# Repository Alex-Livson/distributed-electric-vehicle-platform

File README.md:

# Distributed Electric Vehicle Control and Autonomy Platform

A small-scale electric vehicle electronics platform built around **three custom ESP32-based ECUs and a Raspberry Pi 4 supervisory controller**, connected through a **500 kbps CAN network**.

The project was built as a hands-on study of automotive embedded systems, custom PCB design, distributed vehicle electronics, safety-oriented control, Raspberry Pi development, and computer vision.

## Demo

[Watch the Vehicle Demo](https://youtu.be/MoWJwQRdX8E)

The demonstration includes manual driving, RFID authorization, assisted collision protection, live vehicle telemetry, and OpenCV-assisted autonomous obstacle avoidance.

---

## Project Overview

The vehicle uses a distributed control architecture similar in concept to a simplified electric vehicle.

Instead of one microcontroller handling the entire system, responsibilities are divided between several networked controllers:

* **Battery ECU** – monitors pack voltage, current, temperature, and battery health
* **Sensor ECU** – manages ultrasonic ranging, servo scanning, IMU telemetry, RFID authorization, OLED displays, and the LED matrix
* **Motor ECU** – controls the left and right drive motors
* **Raspberry Pi 4** – acts as the supervisory vehicle computer, hosts the dashboard, manages safety logic, processes CAN telemetry, and runs OpenCV perception

All four nodes communicate over a shared **500 kbps CAN bus**.

---

## Key Features

* Three custom ESP32 ECU PCBs designed in KiCad
* Four-node 500 kbps CAN network
* Raspberry Pi 4 supervisory vehicle controller
* Browser-based real-time vehicle dashboard
* Manual, Assisted, and Autonomous driving modes
* Whole-vehicle voltage, current, and temperature monitoring
* RFID-based vehicle authorization
* Ultrasonic obstacle detection with servo scanning
* OpenCV-assisted autonomous obstacle avoidance
* IMU acceleration, angular velocity, and orientation telemetry
* Differential motor control
* Emergency-stop functionality
* CAN and browser communication watchdogs
* Distance-based collision protection
* Multi-stage overcurrent protection
* Automatic Raspberry Pi and CAN startup

---

# System Architecture

The architecture separates sensing, power monitoring, motor actuation, and higher-level decision making.

```text
                         Raspberry Pi 4
                    Supervisory Vehicle Computer
                              │
                              │
                       500 kbps CAN Bus
                              │
          ┌───────────────────┼───────────────────┐
          │                   │                   │
     Battery ECU          Sensor ECU          Motor ECU
          │                   │                   │
     INA228 + NTC      Ultrasonic / IMU       TB6612FNG
                            RFID             Dual TT Motors
                         OLED Displays
                          LED Matrix
```

The Raspberry Pi receives telemetry from each ECU, applies supervisory safety rules, and transmits the final motor commands to the vehicle.

---

# Custom ECU Hardware

The electronics were first validated on breadboards and then converted into three custom two-layer PCBs.

## Battery ECU

The Battery ECU monitors the electrical health of the complete vehicle.

Hardware includes:

* ESP32-WROOM-32 development board
* INA228 current and voltage monitor
* 10 kΩ NTC thermistor
* CAN transceiver
* Status LED
* Power-distribution connections

The INA228 is positioned near the beginning of the vehicle power path so current measurement represents the entire system.

---

## Sensor ECU

The Sensor ECU manages most of the vehicle's environmental sensing and local user interface.

It controls:

* HC-SR04 ultrasonic distance sensor
* Microservo for left/center/right scanning
* MPU9250 IMU
* MFRC522 RFID reader
* Two 0.96" 128×64 OLED displays
* MAX7219 8×8 LED matrix
* CAN communication

The ultrasonic sensor continuously provides forward and directional range data used by both the safety system and autonomous driving logic.

---

## Motor ECU

The Motor ECU controls two TT gearmotors through a **TB6612FNG dual motor driver**.

Commands are transmitted as independent signed left and right motor percentages, allowing:

* Forward driving
* Reverse driving
* Differential steering
* In-place turning

The ECU also reports motor status back to the Raspberry Pi over CAN.

---

# PCB Development

All three ECU boards were designed in **KiCad**.

The PCB development process included:

1. Breadboard hardware validation
2. Schematic capture
3. Custom through-hole footprint creation
4. Two-layer PCB layout
5. Ground-plane design
6. Power trace sizing
7. ESP32 antenna keep-out
8. Design Rule Check
9. Fabrication through JLCPCB
10. Hand soldering and hardware bring-up

Typical trace widths were approximately:

* **0.25 mm** for signals
* **0.75 mm** for 3.3 V distribution
* **1.0 mm** for higher-current 5 V paths

The bottom layer was used primarily as a ground plane.

---

# CAN Network

The completed vehicle contains four CAN nodes operating at **500 kbps**.

The Battery ECU and Raspberry Pi are located at the two ends of the physical bus and provide termination.

A powered-off measurement across CAN-H and CAN-L is approximately **60 Ω**, corresponding to two effective 120 Ω terminating resistors.

## CAN Message Map

| CAN ID  | Direction        | Purpose                                            |
| ------- | ---------------- | -------------------------------------------------- |
| `0x100` | Battery ECU → Pi | Battery voltage, current, and temperature          |
| `0x200` | Sensor ECU → Pi  | Sensor status, ultrasonic range, RFID state        |
| `0x201` | Sensor ECU → Pi  | Accelerometer X/Y/Z                                |
| `0x202` | Sensor ECU → Pi  | Angular velocity X/Y/Z                             |
| `0x203` | Sensor ECU → Pi  | Roll, pitch, and yaw                               |
| `0x204` | Sensor ECU → Pi  | Left, center, and right ultrasonic ranges          |
| `0x300` | Motor ECU → Pi   | Motor output and ECU status                        |
| `0x400` | Pi → Vehicle     | Drive command, mode, speed limit, and safety state |
| `0x401` | Pi → Sensor ECU  | Lock/unlock request                                |

Detailed CAN payload definitions are available in the full engineering report.

---

# Raspberry Pi Vehicle Computer

The vehicle computer is a **Raspberry Pi 4 Model B with 1 GB RAM** running Raspberry Pi OS Lite.

The main controller is written in Python and integrates:

* Linux SocketCAN
* Flask
* OpenCV
* Threaded CAN reception
* Safety management
* Vehicle state tracking
* Autonomous decision making
* Browser control
* Camera streaming

The Pi runs a supervisory control loop every **20 ms**, corresponding to approximately **50 Hz**.

CAN and the main vehicle application are configured to initialize automatically when the Raspberry Pi boots.

---

# Web Dashboard

The Raspberry Pi hosts a local browser-based vehicle interface.

The dashboard displays:

* Live forward camera
* Drive mode
* Motor requests and feedback
* Pack voltage
* Pack current
* Battery temperature
* Ultrasonic distance
* Ultrasonic radar visualization
* IMU orientation
* Acceleration
* ECU network health
* RFID lock state
* E-stop state
* Current limiting
* Wall intervention
* System event history

Manual and Assisted driving are controlled using **WASD**, with an adjustable 0–100% speed limit.

---

# Drive Modes

## Manual

Manual mode gives the driver direct WASD control over the differential drive system.

A forward collision stop remains active even in Manual mode so the vehicle cannot continue driving directly into a very close obstacle during testing.

---

## Assisted

Assisted mode keeps manual WASD control while adding distance-based collision protection.

| Forward Distance   | Vehicle Response                     |
| ------------------ | ------------------------------------ |
| Greater than 40 cm | Normal requested output              |
| 20–40 cm           | Forward output progressively reduced |
| 12–20 cm           | Positive forward commands removed    |
| Less than 12 cm    | Hard forward collision intervention  |

This allows the driver to remain in control while the supervisory system limits unsafe commands.

---

## Autonomous

Autonomous mode combines **ultrasonic ranging and OpenCV computer vision**.

The ultrasonic sensor determines when an obstacle is physically close.

When an obstacle requires avoidance, OpenCV evaluates the left and right portions of the camera image to estimate which side appears less obstructed.

The vehicle then:

1. Detects the obstacle
2. Determines the clearer direction
3. Reverses briefly to create turning clearance
4. Turns toward the clearer side
5. Resumes forward driving

If the camera result is unavailable or nearly tied, the vehicle falls back to the left/right ultrasonic scan.

The system is intended as **vision-assisted obstacle avoidance**, rather than full autonomous driving or localization.

---

# OpenCV Perception

The OpenCV pipeline processes the lower portion of the forward camera image.

Processing includes:

* Grayscale conversion
* Gaussian blur
* Canny edge detection
* Edge dilation
* Left/right image segmentation
* Weighted edge-density comparison

The lower portion of each image region is weighted more heavily because it is more likely to contain obstacles in the vehicle's immediate path.

---

# Safety Architecture

All requested motor commands pass through a supervisory safety manager before being transmitted to the Motor ECU.

| Protection           | Behavior                                                       |
| -------------------- | -------------------------------------------------------------- |
| RFID authorization   | Blocks vehicle movement while locked                           |
| Emergency stop       | Overrides all drive modes                                      |
| Browser watchdog     | Stops Manual/Assisted control after 500 ms without fresh input |
| Battery ECU timeout  | Blocks motion if critical battery telemetry becomes stale      |
| Sensor ECU timeout   | Blocks motion if critical sensor telemetry becomes stale       |
| Wall protection      | Slows or stops forward movement near obstacles                 |
| Current warning      | Reduces motor output above 4.75 A                              |
| Current limiting     | Stronger output reduction above 5.25 A                         |
| Overcurrent shutdown | Stops vehicle above 5.50 A and applies a 1.5 s cooldown        |

The system follows a fail-safe principle: if the controller does not have enough current information to determine that movement is safe, the preferred state is no movement.

---

# Final System Performance

| Metric                        | Result                   |
| ----------------------------- | ------------------------ |
| CAN bitrate                   | 500 kbps                 |
| Pi supervisory loop           | 50 Hz                    |
| Local browser control latency | ~20–30 ms                |
| Idle current                  | ~0.8–0.9 A               |
| Typical driving current       | ~1.2–1.3 A               |
| Peak observed current         | ~1.6 A                   |
| Battery runtime               | ~1 hour                  |
| Battery                       | 2S 7.4 V, 2000 mAh       |
| Vehicle dimensions            | 24 × 19 × 19 cm          |
| Vehicle mass                  | ~872 g including battery |
| Estimated maximum speed       | ~4 ft/s                  |
| Approximate project cost      | ~$300                    |

Maximum physical speed is estimated rather than encoder-measured because the current prototype does not contain wheel encoders.

---

# Full Engineering Report

A complete engineering report documents the project architecture, PCB development, electrical system, CAN protocol, software, safety design, debugging process, validation, and future improvements.

**[Read the full Engineering Report](docs/Engineering_Report.pdf)** (download pdf!)

---

# Project Development

The project was developed between **July 11 and August 17, 2026**.

I designed the system architecture, defined the ECU responsibilities and CAN protocol, created all three PCB schematics and layouts, assembled and soldered the boards, integrated the vehicle electronics, and performed final system testing.

The project uses standard hardware and software libraries for common peripheral interfaces and software functionality. Development also included external code review and troubleshooting assistance.

---

## Documentation

* **[Engineering Report](docs/Engineering_Report.pdf)**
* **[Vehicle Demonstration](https://youtu.be/MoWJwQRdX8E)**

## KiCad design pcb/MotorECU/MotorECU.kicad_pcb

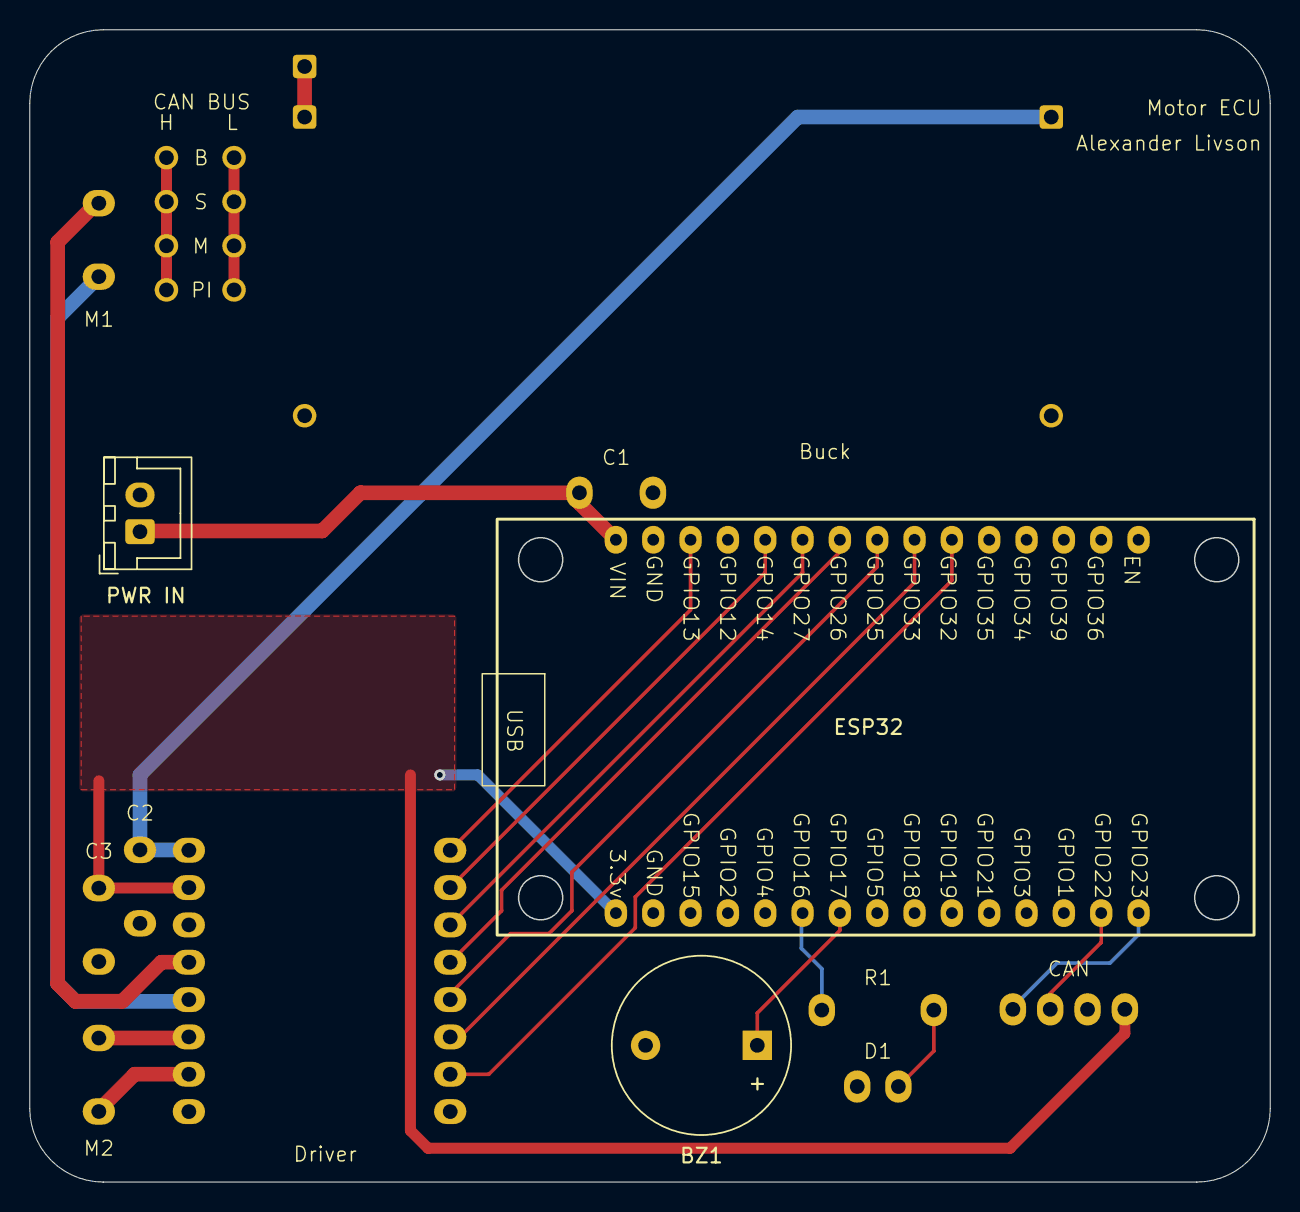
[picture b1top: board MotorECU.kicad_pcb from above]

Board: 2 copper layers, 84.4 x 78.4 mm, 13 parts (0 on the bottom side), 20 nets.

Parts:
BZ1: Buzzer; Buzzer_12x9.5RM7.6
Buck: Buck Converter
C1, C3: 0.1uF; 0.1 Ceramic Capacitor
C2: 470uF; Elytrolytic Capacitor
CAN: SN65HVD230; SN65HVD230 CAN Module
D1: LED
Driver: TB6612FNG; TB6612FNG DC Motor Driver
ESP32: ESP32_30pin
M1, M2: Motor_DC; DC_Motor
PWR IN: JST_XH_B2B-XH-A_1x02_P2.50mm_Vertical
R1: 330; Resistor

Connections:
+3.3V: C3.1, CAN.1 (3.3V), Driver.2 (VCC), ESP32.16 (3.3v)
+5V: Buck.3 (OUT+), C2.1, Driver.1 (VM)
/5V_ESP: C1.1, ESP32.1 (VIN), PWR IN.1
/A1: Driver.4 (A1), M1.1 (+)
/A2: Driver.5 (A2), M1.2 (-)
/B1: Driver.6 (B1), M2.1 (+)
/B2: Driver.7 (B2), M2.2 (-)
GND: BZ1.2 (-), Buck.2 (IN-), Buck.4 (OUT-), C1.2, C2.2, C3.2, CAN.2 (GND), D1.1 (K), Driver.3 (GND), ESP32.2 (GND), PWR IN.2
unnamed: BZ1.1 (+), ESP32.22 (GPIO17)
unnamed: D1.2 (A), R1.2
unnamed: Driver.16 (PWMA), ESP32.3 (GPIO13)
unnamed: Driver.15 (AIN2), ESP32.5 (GPIO14)
unnamed: ESP32.21 (GPIO16), R1.1
unnamed: CAN.3 (CAN_RX), ESP32.29 (GPIO22)
unnamed: CAN.4 (CAN_TX), ESP32.30 (GPIO23)
unnamed: Driver.12 (BIN1), ESP32.8 (GPIO25)
unnamed: Driver.13 (STBY), ESP32.7 (GPIO26)
unnamed: Driver.14 (AIN1), ESP32.6 (GPIO27)
unnamed: Driver.10 (PWMB), ESP32.10 (GPIO32)
unnamed: Driver.11 (BIN2), ESP32.9 (GPIO33)

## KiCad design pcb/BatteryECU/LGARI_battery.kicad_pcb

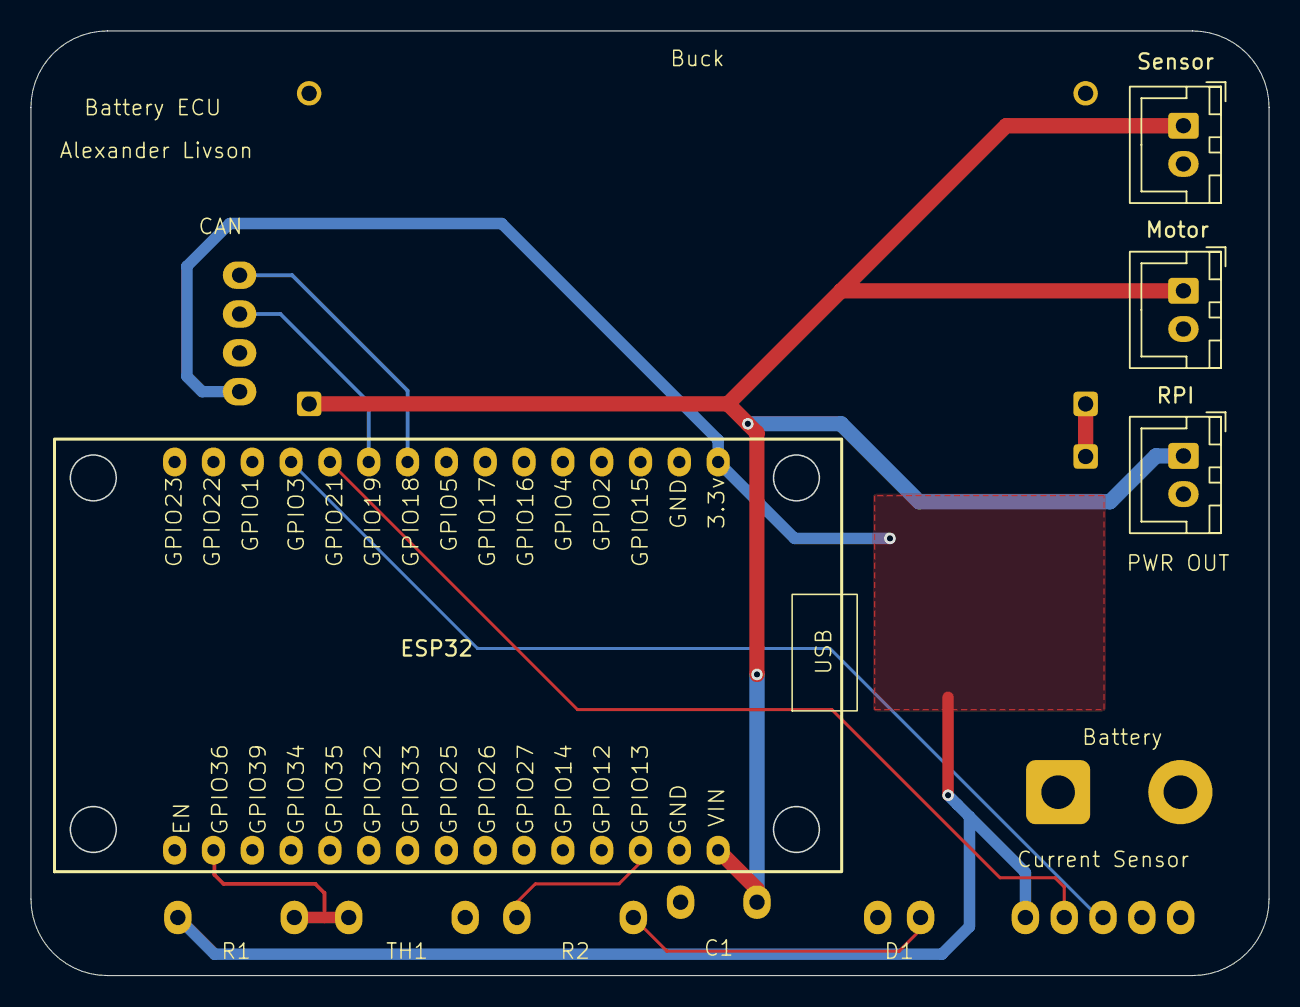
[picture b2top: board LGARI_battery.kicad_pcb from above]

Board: 2 copper layers, 81.0 x 61.8 mm, 13 parts (0 on the bottom side), 10 nets.

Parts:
Battery: XT60; Battery
Buck: Buck Converter
C1: 0.1uF; 0.1 Ceramic Capacitor
CAN: SN65HVD230; SN65HVD230 CAN Module
Current Sensor: INA228
D1: LED
ESP32: ESP32_30pin
Motor: JST_XH_B2B-XH-A_1x02_P2.50mm_Vertical
R1: 10k; Resistor
R2: 330; Resistor
RPI: JST_XH_B2B-XH-A_1x02_P2.50mm_Vertical
Sensor: JST_XH_B2B-XH-A_1x02_P2.50mm_Vertical
TH1: Thermistor_US; Thermistor

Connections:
+3.3V: CAN.1 (3.3V), Current Sensor.5 (VCC), ESP32.16 (3.3v), R1.1
+5V: Buck.3 (OUT+), C1.1, ESP32.1 (VIN), Motor.1, RPI.1, Sensor.1
/SCL: Current Sensor.3 (SCL), ESP32.27 (GPIO3)
/SDA: Current Sensor.4 (SDA), ESP32.26 (GPIO21)
GND: Battery.2, Buck.2 (IN-), Buck.4 (OUT-), C1.2, CAN.2 (GND), Current Sensor.1 (GND), D1.1 (K), ESP32.2 (GND), Motor.2, RPI.2, Sensor.2, TH1.2
unnamed: D1.2 (A), R2.2
unnamed: ESP32.3 (GPIO13), R2.1
unnamed: CAN.4 (CAN_TX), ESP32.24 (GPIO18)
unnamed: CAN.3 (CAN_RX), ESP32.25 (GPIO19)
unnamed: ESP32.14 (GPIO36), R1.2, TH1.1

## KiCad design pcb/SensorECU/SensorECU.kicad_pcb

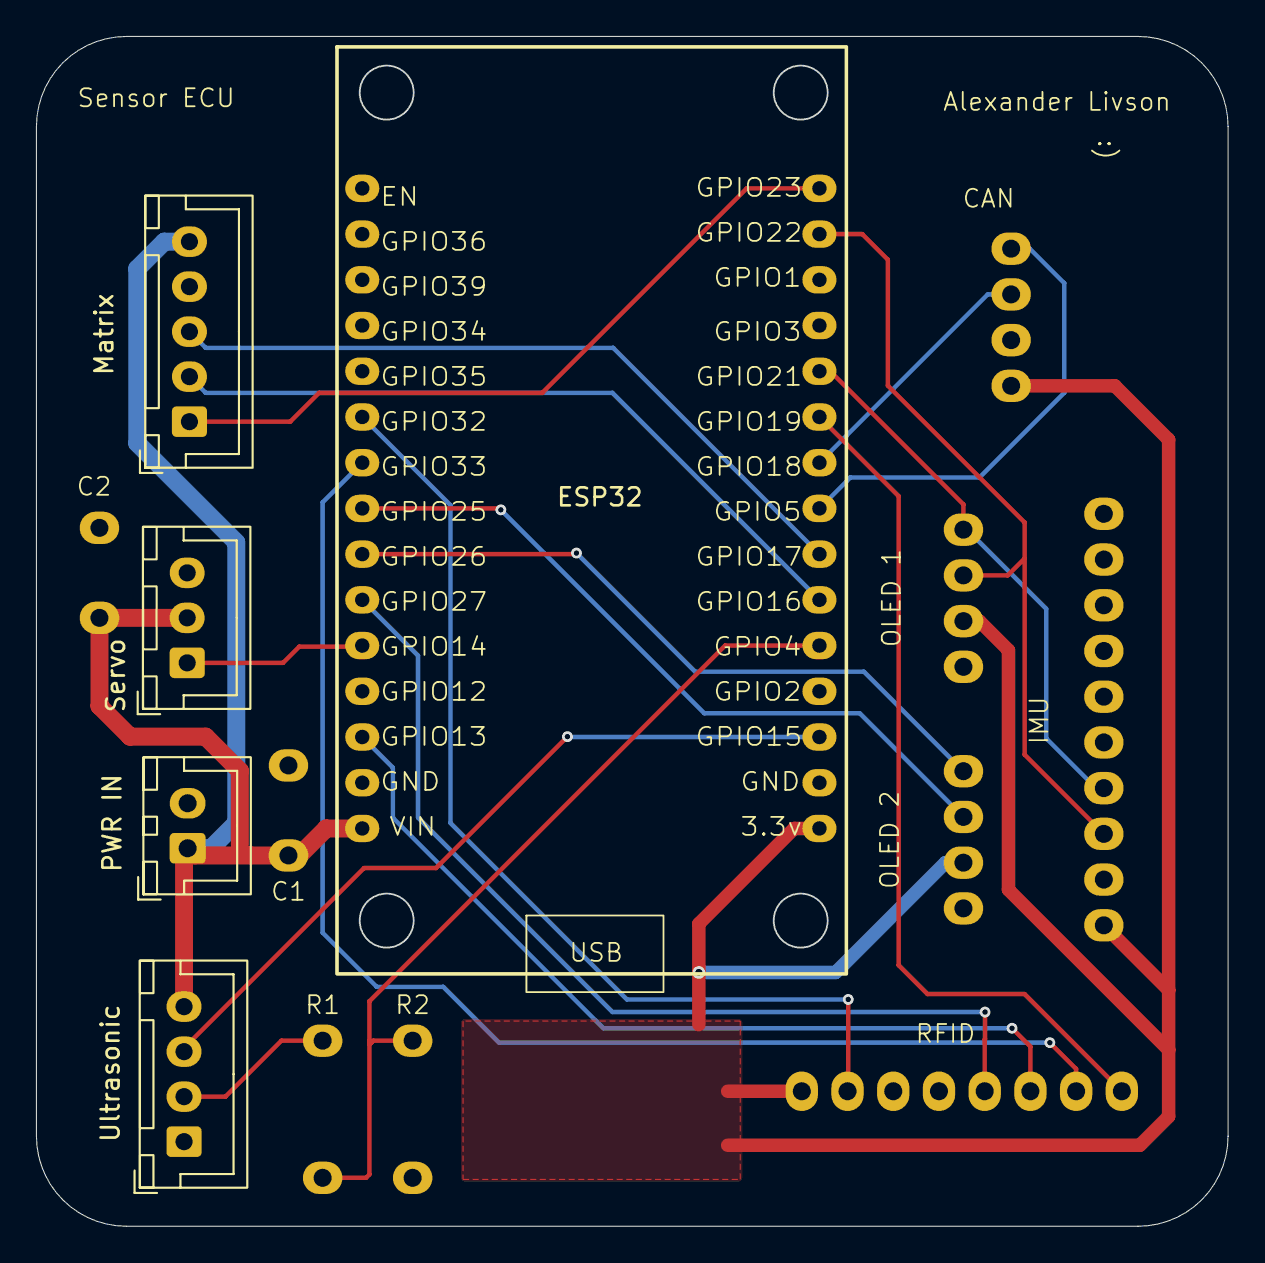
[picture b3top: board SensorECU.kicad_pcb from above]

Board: 2 copper layers, 66.2 x 66.1 mm, 13 parts (0 on the bottom side), 21 nets.

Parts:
C1: 0.1uF; 0.1 Ceramic Capacitor
C2: 470uF; Elytrolytic Capacitor
CAN: SN65HVD230; SN65HVD230 CAN Module
ESP32: ESP32_30pin
IMU: MPU-9250; IMU_MPU-9250
Matrix: MAX7219; JST_XH_B5B-XH-A_1x05_P2.50mm_Vertical
OLED 1: OLED 1; 0.96 in. OLED
OLED 2: OLED 2; 0.96 in. OLED
R1: 1k; Resistor
R2: 2k; Resistor
RFID: RFID; RFID-RC522
Servo: Motor_Servo; JST_XH_B3B-XH-A_1x03_P2.50mm_Vertical
Ultrasonic: HC-SR04; JST_XH_B4B-XH-A_1x04_P2.50mm_Vertical

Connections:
+3.3V: CAN.1 (3.3V), ESP32.16 (3.3v), IMU.1 (VCC), OLED 1.2 (VCC), OLED 2.2 (VCC), RFID.8 (3.3V)
+5V: C1.1, C2.1, ESP32.1 (VIN), Matrix.5 (VCC), Servo.2 (+), Ultrasonic.4 (VCC)
/GPIO19: ESP32.25 (GPIO19), RFID.1 (SDA)
/PWM_Servo: ESP32.5 (GPIO14), Servo.1 (PWM)
/SCL_1: ESP32.29 (GPIO22), IMU.3 (SCL), OLED 1.3 (SCL)
/SCL_2: ESP32.8 (GPIO25), OLED 2.3 (SCL)
/SDA_1: ESP32.26 (GPIO21), IMU.4 (SDA), OLED 1.4 (SDA)
/SDA_2: ESP32.7 (GPIO26), OLED 2.4 (SDA)
GND: C1.2, C2.2, CAN.2 (GND), ESP32.2 (GND), IMU.2 (GND), Matrix.4 (GND), OLED 1.1 (GND), OLED 2.1 (GND), R2.2, RFID.6 (GND), Servo.3 (-), Ultrasonic.1 (GND)
unnamed: ESP32.20 (GPIO4), R1.2, R2.1
unnamed: CAN.4 (CAN_TX), ESP32.23 (GPIO5)
unnamed: ESP32.3 (GPIO13), RFID.3 (MOSI)
unnamed: ESP32.18 (GPIO15), Ultrasonic.3 (Trig)
unnamed: ESP32.21 (GPIO16), Matrix.2 (CS)
unnamed: ESP32.22 (GPIO17), Matrix.3 (DIN)
unnamed: CAN.3 (CAN_RX), ESP32.24 (GPIO18)
unnamed: ESP32.30 (GPIO23), Matrix.1 (CLK)
unnamed: ESP32.6 (GPIO27), RFID.4 (MISO)
unnamed: ESP32.10 (GPIO32), RFID.7 (RST)
unnamed: ESP32.9 (GPIO33), RFID.2 (SCK)
unnamed: R1.1, Ultrasonic.2 (Echo)
